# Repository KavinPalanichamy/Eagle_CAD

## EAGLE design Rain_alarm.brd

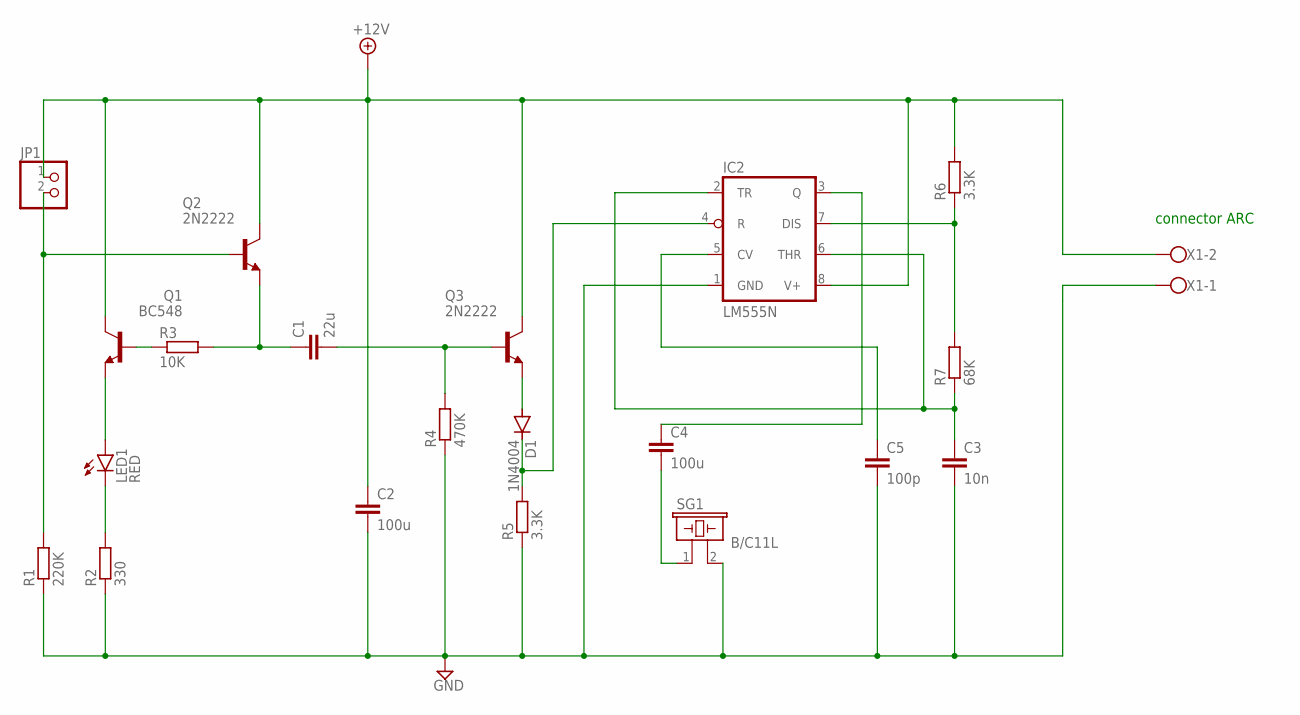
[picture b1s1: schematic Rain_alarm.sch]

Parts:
C1: 22u; C025-025X050
C2, C4: 100u; C025-025X050
C3: 10n; C025-025X050
C5: 100p; C025-025X050
D1: 1N4004; DO41-10
IC2: LM555N; DIL08
JP1: PINHD-1X2; 1X02
LED1: RED; LED3MM
Q1: BC548; TO92-EBC
Q2, Q3: 2N2222; TO18
R1: 220K; 0204/7
R2: 330; 0204/7
R3: 10K; 0204/7
R4: 470K; 0204/7
R5, R6: 3.3K; 0204/7
R7: 68K; 0204/7
SG1: B/C11L
X1: W237-102

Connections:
+12V: C2.1, IC2.8 (V+), JP1.1, Q1.C, Q2.3 (C), Q3.3 (C), R6.2, X1.2
GND: C2.2, C3.2, C5.2, IC2.1 (GND), R1.1, R2.1, R4.1, R5.1, SG1.2, X1.1
unnamed: IC2.7 (DIS), R6.1, R7.2
unnamed: C3.1, IC2.2 (TR), IC2.6 (THR), R7.1
unnamed: C1.2, Q3.2 (B), R4.2
unnamed: C1.1, Q2.1 (E), R3.2
unnamed: D1.A, Q3.1 (E)
unnamed: D1.C, IC2.4 (R), R5.2
unnamed: JP1.2, Q2.2 (B), R1.2
unnamed: LED1.K (C), R2.2
unnamed: LED1.A, Q1.E
unnamed: Q1.B, R3.1
unnamed: C4.1, IC2.3 (Q)
unnamed: C4.2, SG1.1
unnamed: C5.1, IC2.5 (CV)

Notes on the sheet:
connector ARC

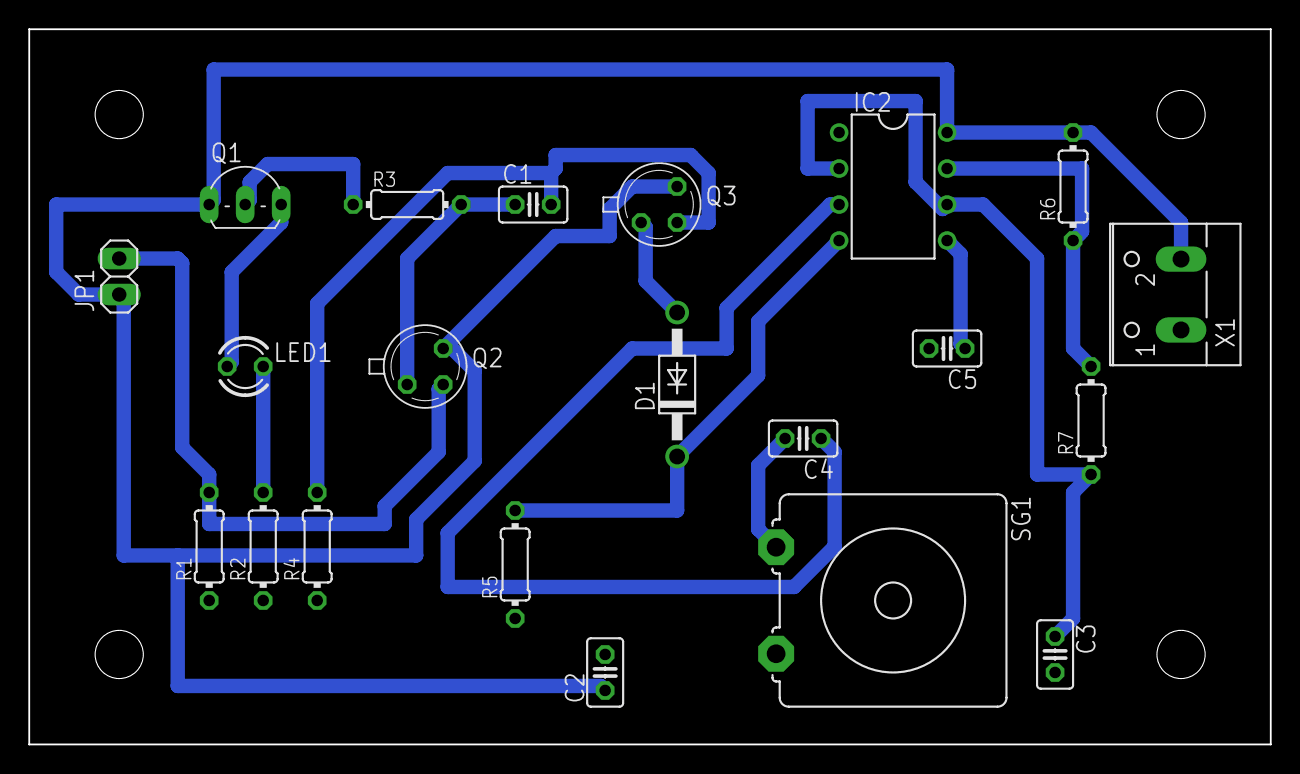
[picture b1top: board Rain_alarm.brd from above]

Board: 2 copper layers, 87.6 x 50.5 mm, 21 parts (0 on the bottom side), 15 nets.

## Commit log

2023-05-20 Rain alarm
    Contains files related to rain alarm project
2023-05-20 Change file_name
2023-05-20 Image_files
